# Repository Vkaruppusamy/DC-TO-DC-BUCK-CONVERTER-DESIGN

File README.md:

# DC-TO-DC-BUCK-CONVERTER-DESIGN
This is a model for the dc to dc buck converter design using KICAD 8.0 completley 
The sample models are here

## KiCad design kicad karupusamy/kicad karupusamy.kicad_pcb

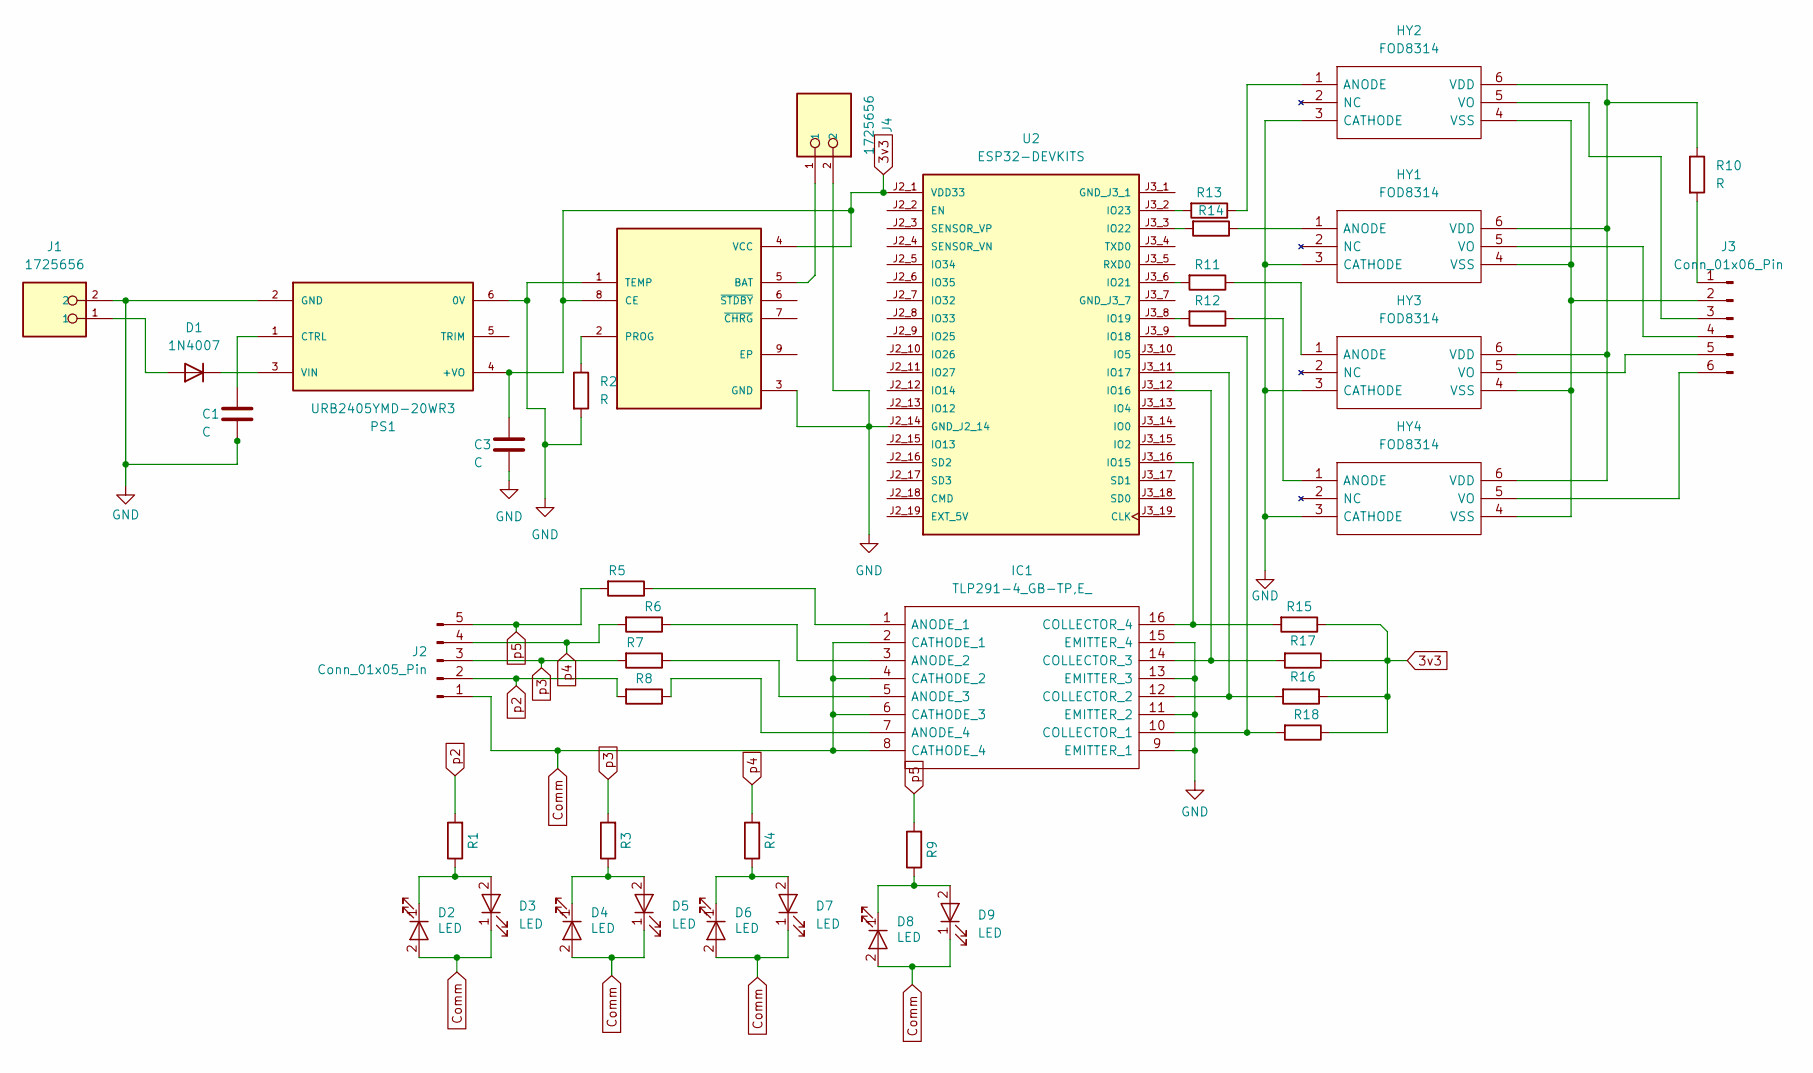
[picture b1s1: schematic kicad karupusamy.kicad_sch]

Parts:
C1, C3: C; C_Radial_D4.0mm_H5.0mm_P1.50mm
D1: 1N4007; D_DO-41_SOD81_P10.16mm_Horizontal
D2, D3, D4, D5, D6, D7, D8, D9: LED; LED_D3.0mm
HY1, HY2, HY3, HY4: FOD8314; SOIC127P970X348-6N; Manufacturer_Part_Number FOD8314; Mouser Part Number 512-FOD8314
IC1: TLP291-4_GB-TP,E_; SOIC127P700X230-16N; Manufacturer_Part_Number TLP291-4(GB-TP,E); Mouser Part Number 757-TLP2914GB-TPE
J1, J4: 1725656; PinHeader_1x02_P2.54mm_Vertical; PARTREV 03.03.2021
J2: Conn_01x05_Pin; PinHeader_1x05_P2.54mm_Vertical
J3: Conn_01x06_Pin; PinHeader_1x06_P2.54mm_Vertical
PS1: URB2405YMD-20WR3; CONV_URB2405YMD-20WR3; PARTREV 2019.10.16-A/4
R1, R2, R3, R4, R5, R7, R8, R9, R10, R11, R12, R13, R14, R15, R16, R17, R18: R; R_Axial_DIN0204_L3.6mm_D1.6mm_P7.62mm_Horizontal
R6: R_Axial_DIN0204_L3.6mm_D1.6mm_P7.62mm_Horizontal
U1: TP4056; TP4056-18650
U2: ESP32-DEVKITS; MODULE_ESP32-DEVKITS; PARTREV 1.1

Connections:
3v3: C3.1, PS1.4 (+VO), R15.1, R16.1, R17.1, R18.1, U1.4 (VCC), U1.8 (CE), U2.J2_1 (VDD33)
Comm: D2.2 (A), D3.1 (K), D4.2 (A), D5.1 (K), D6.2 (A), D7.1 (K), D8.2 (A), D9.1 (K), IC1.2 (CATHODE_1), IC1.4 (CATHODE_2), IC1.6 (CATHODE_3), IC1.8 (CATHODE_4), J2.1
GND: C1.2, C3.2, HY1.3 (CATHODE), HY2.3 (CATHODE), HY3.3 (CATHODE), HY4.3 (CATHODE), IC1.9 (EMITTER_1), IC1.11 (EMITTER_2), IC1.13 (EMITTER_3), IC1.15 (EMITTER_4), J1.2, J4.2, PS1.2 (GND), PS1.6 (0V), R2.2, U1.1 (TEMP), U1.3 (GND), U2.J2_14 (GND_J2_14)
unnamed: D1.2 (A), J1.1
unnamed: D1.1 (K), PS1.3 (VIN)
unnamed: D2.1 (K), D3.2 (A), R1.1
unnamed: D4.1 (K), D5.2 (A), R3.1
unnamed: D6.1 (K), D7.2 (A), R4.1
unnamed: D8.1 (K), D9.2 (A), R9.1
unnamed: HY1.1 (ANODE), R14.1
unnamed: HY1.6 (VDD), HY2.6 (VDD), HY3.6 (VDD), HY4.6 (VDD), R10.1
unnamed: HY1.5 (VO), J3.4
unnamed: HY1.4 (VSS), HY2.4 (VSS), HY3.4 (VSS), HY4.4 (VSS), J3.2
unnamed: HY2.1 (ANODE), R13.1
unnamed: HY2.5 (VO), J3.3
unnamed: HY3.1 (ANODE), R11.1
unnamed: HY3.5 (VO), J3.5
unnamed: HY4.1 (ANODE), R12.1
unnamed: HY4.5 (VO), J3.6
unnamed: IC1.1 (ANODE_1), R5.1
unnamed: IC1.3 (ANODE_2), R6.1
unnamed: IC1.5 (ANODE_3), R7.1
unnamed: IC1.7 (ANODE_4), R8.1
unnamed: IC1.10 (COLLECTOR_1), R18.2, U2.J3_9 (IO18)
unnamed: IC1.12 (COLLECTOR_2), R16.2, U2.J3_11 (IO17)
unnamed: IC1.14 (COLLECTOR_3), R17.2, U2.J3_12 (IO16)
unnamed: IC1.16 (COLLECTOR_4), R15.2, U2.J3_16 (IO15)
unnamed: J3.1, R10.2
unnamed: C1.1, PS1.1 (CTRL)
unnamed: J4.1, U1.5 (BAT)
unnamed: R2.1, U1.2 (PROG)
unnamed: R12.2, U2.J3_8 (IO19)
unnamed: R11.2, U2.J3_6 (IO21)
unnamed: R14.2, U2.J3_3 (IO22)
unnamed: R13.2, U2.J3_2 (IO23)
p2: J2.2, R1.2, R8.2
p3: J2.3, R3.2, R7.2
p4: J2.4, R4.2, R6.2
p5: J2.5, R5.2, R9.2

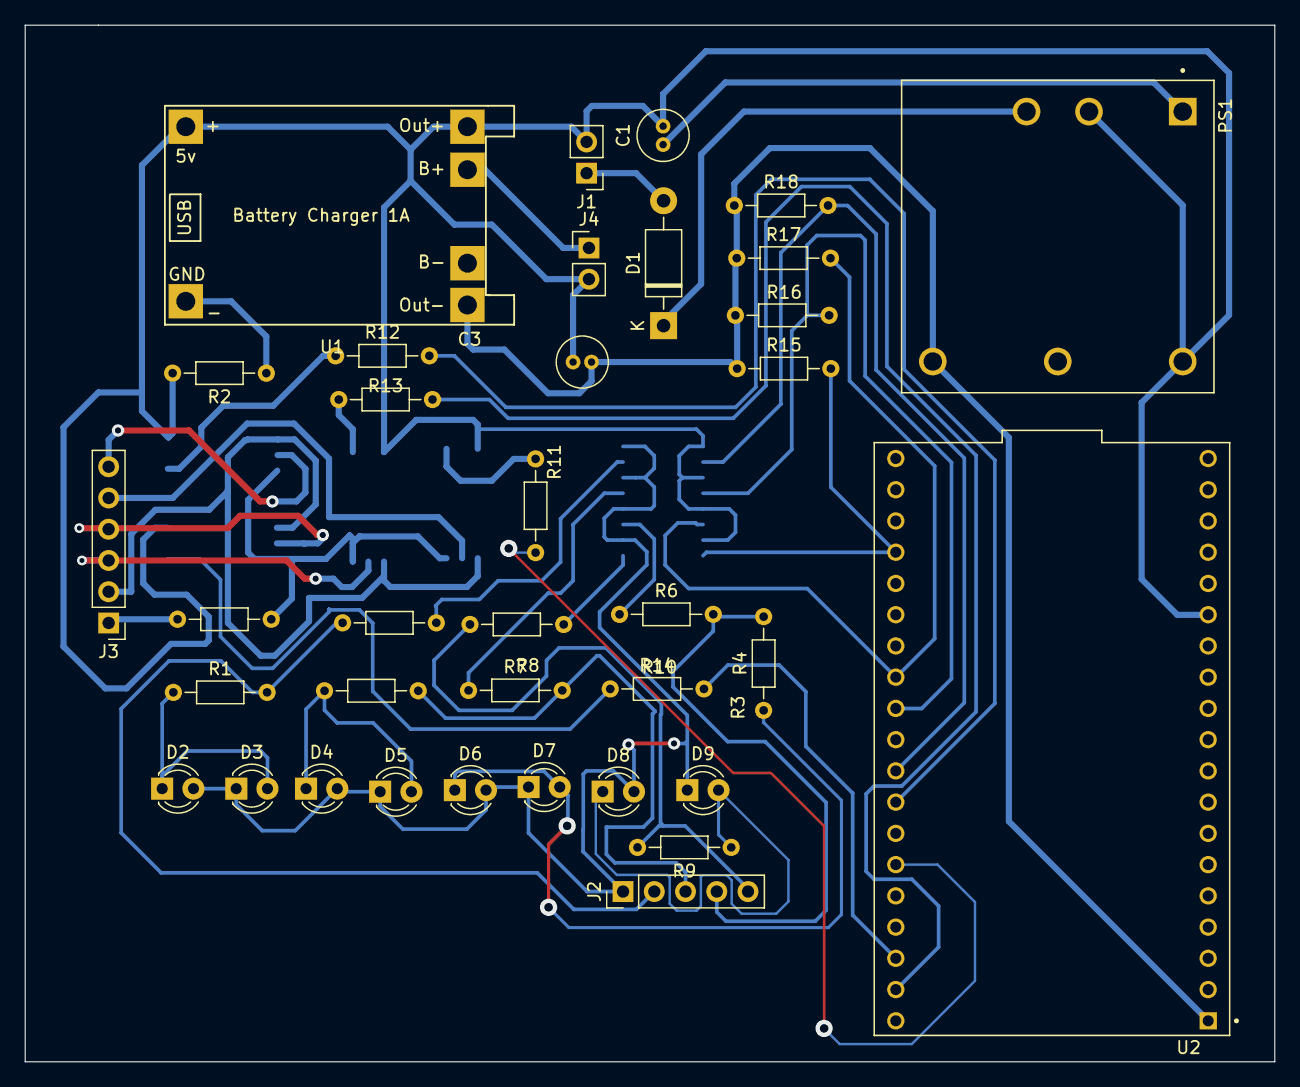
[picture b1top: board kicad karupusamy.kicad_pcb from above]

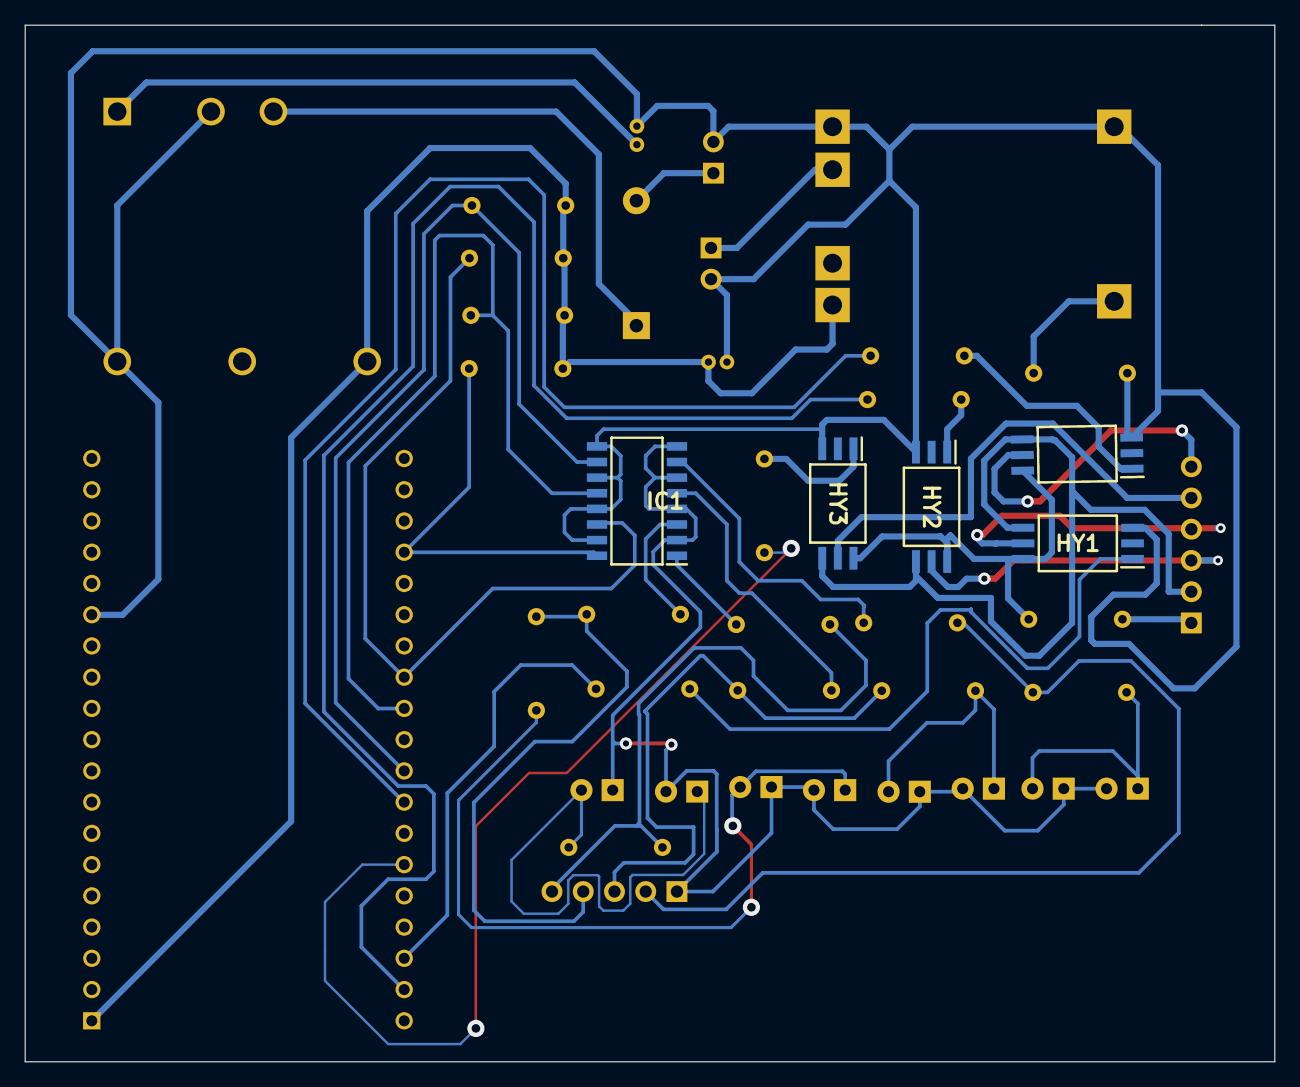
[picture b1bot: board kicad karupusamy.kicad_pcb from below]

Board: 2 copper layers, 101.6 x 84.3 mm, 41 parts (5 on the bottom side), 39 nets.
